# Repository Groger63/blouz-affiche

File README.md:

# blouz-affiche
affiche des infos sur ma blouse utbm

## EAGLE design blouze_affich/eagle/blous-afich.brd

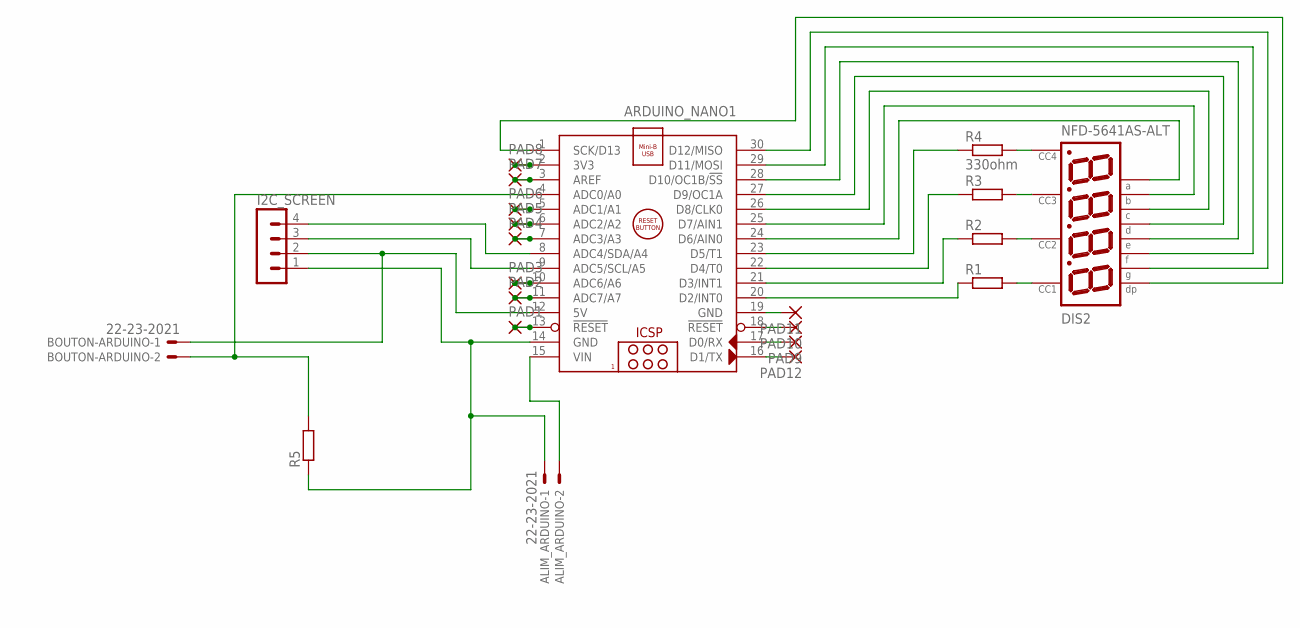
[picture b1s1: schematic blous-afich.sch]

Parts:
ALIM_ARDUINO: 22-23-2021
ARDUINO_NANO1: ARDUINO_NANO
BOUTON-ARDUINO: 22-23-2021
DIS2: NFD-5641AS-ALT; NFD-5641
I2C_SCREEN: MA04-1
PAD1, PAD2, PAD3, PAD4, PAD5, PAD6, PAD7, PAD8, PAD9, PAD10, PAD11, PAD12: 1,6/0,8
R1, R2, R3, R5: R-EU_0207/7; 0207/7
R4: 330ohm; 0207/7

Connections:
unnamed: ARDUINO_NANO1.20 (D2/INT0), R1.1
unnamed: ARDUINO_NANO1.21 (D3/INT1), R2.1
unnamed: ARDUINO_NANO1.22 (D4/T0), R3.1
unnamed: ARDUINO_NANO1.23 (D5/T1), R4.1
unnamed: DIS2.P$6, R4.2
unnamed: DIS2.P$8, R3.2
unnamed: DIS2.P$9, R2.2
unnamed: DIS2.P$12, R1.2
unnamed: ARDUINO_NANO1.24 (D6/AIN0), DIS2.P$11
unnamed: ARDUINO_NANO1.25 (D7/AIN1), DIS2.P$7
unnamed: ARDUINO_NANO1.26 (D8/CLK0), DIS2.P$4
unnamed: ARDUINO_NANO1.27 (D9/OC1A), DIS2.P$2
unnamed: ARDUINO_NANO1.28 (D10/OC1B/!SS), DIS2.P$1
unnamed: ARDUINO_NANO1.29 (D11/MOSI), DIS2.P$10
unnamed: ARDUINO_NANO1.30 (D12/MISO), DIS2.P$5
unnamed: ARDUINO_NANO1.1 (SCK/D13), DIS2.P$3
unnamed: ARDUINO_NANO1.8 (ADC4/SDA/A4), I2C_SCREEN.4
unnamed: ARDUINO_NANO1.9 (ADC5/SCL/A5), I2C_SCREEN.3
unnamed: ARDUINO_NANO1.12 (5V), BOUTON-ARDUINO.1, I2C_SCREEN.2
unnamed: ALIM_ARDUINO.1, ARDUINO_NANO1.14 (GND), I2C_SCREEN.1, R5.1
unnamed: ARDUINO_NANO1.4 (ADC0/A0), BOUTON-ARDUINO.2, R5.2
unnamed: ALIM_ARDUINO.2, ARDUINO_NANO1.15 (VIN)
unnamed: ARDUINO_NANO1.2 (3V3), PAD8.1
unnamed: ARDUINO_NANO1.3 (AREF), PAD7.1
unnamed: ARDUINO_NANO1.5 (ADC1/A1), PAD6.1
unnamed: ARDUINO_NANO1.6 (ADC2/A2), PAD5.1
unnamed: ARDUINO_NANO1.7 (ADC3/A3), PAD4.1
unnamed: ARDUINO_NANO1.10 (ADC6/A6), PAD3.1
unnamed: ARDUINO_NANO1.11 (ADC7/A7), PAD2.1
unnamed: ARDUINO_NANO1.19 (GND), PAD11.1
unnamed: ARDUINO_NANO1.18 (!RESET), PAD10.1
unnamed: ARDUINO_NANO1.17 (D0/RX), PAD9.1
unnamed: ARDUINO_NANO1.16 (D1/TX), PAD12.1
unnamed: ARDUINO_NANO1.13 (!RESET), PAD1.1

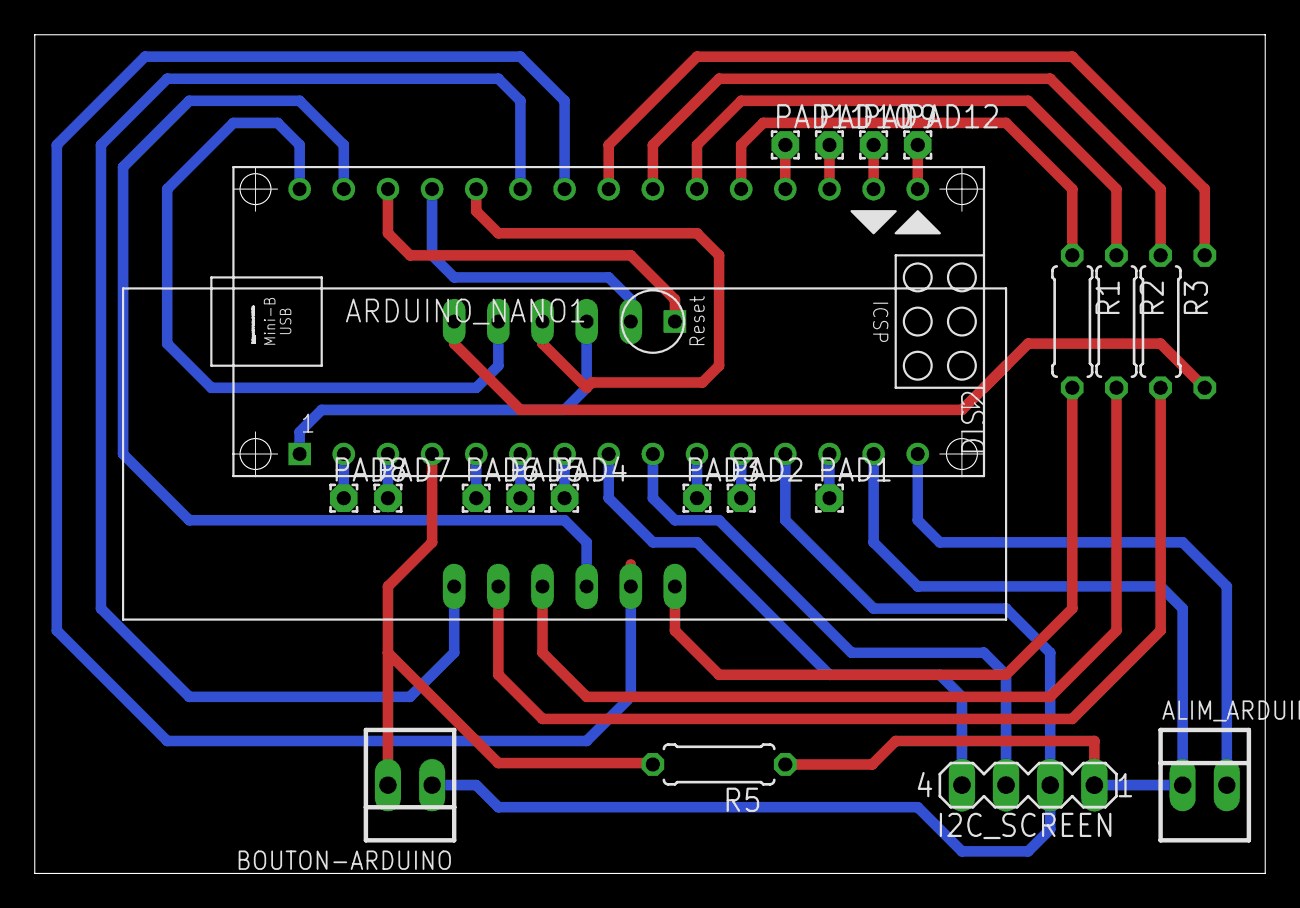
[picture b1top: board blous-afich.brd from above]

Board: 2 copper layers, 70.8 x 48.2 mm, 22 parts (1 on the bottom side), 34 nets.

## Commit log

2017-08-26 quelques modifications après installation, nettoyage de code, ajout de conneries...
2017-08-26 globalement tout est fonctionnel
2017-10-15 Ajouté le sch&ma de cablage de l'écran 7seg
2017-11-16 petite mise à jour des fonctions (ou pas) et ajout de schémas eagle pour faire un PCB à partir de ce bazard.
